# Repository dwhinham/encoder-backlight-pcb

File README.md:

# Rotary encoder backlight board

This simple board allows you to neatly and painlessly install LEDs on top of a rotary encoder for use with transparent/translucent knobs.

I designed this board when building a [MIDIbox SID synthesizer based on the MB6582 design][midibox-sid]. The idea was inspired by [Hawkeye's control surface build tutorial for the MB6582][knob-backlight-tutorial], but I didn't think I'd personally be able to do a very neat job with enamel wire, and so I decided to design a simple PCB to make it easier to achieve this kind of lighting.

The PCB has been verified to fit perfectly over [Alpha Taiwan RE160F-40E3-20A-24P-003][alpha-encoder] and [Bourns PEC16-4220F-N0024][bourns-encoder].

## Where can I get them?

- I have several spare sets available to anyone who wants them - [contact me on Twitter][twitter] if you'd like to buy some!
- I've also added the PCB to [OSH Park][osh-park] as a shared project if you'd like to order from there.
- Alternatively, you can download this repository and place your own order with a PCB fab service.

## Installation

The PCB has space for three surface-mount LEDs and one resistor. The size of all parts is **0603 imperial (1608 metric)**.

There are multiple **+ (positive)** terminals that you can use to daisy-chain multiple PCBs together if you need to.

### Choosing the resistor value

The three LEDs are wired in series, and share a common resistor (`R1`). The proper value for `R1` will vary depending on the specifications of your LED and the voltage of your power source.

If your LEDs have a low enough voltage drop, you may be able to just bridge `R1` (or use a 0 ohm resistor) and use a 5V power source. The [amber LEDs I used][amber-leds] did not light up at all this way however, and so I chose to use a 9V source instead.

You can use a [simple LED calculator][led-wizard] to help choose the right value for `R1`. In my case, using the datasheet for [my amber LEDs][amber-leds] I entered the following information into the calculator:

- Source voltage: **9V**
- Diode forward voltage: **2V**
- Diode forward current (mA): **20mA**
- Number of LEDs in your array: **3**

The result was **150 ohms**, and so that's the value I used for `R1`.

### Attaching the board to the encoder

1. Solder a wire to one or more of the **+ (positive)** terminal of the PCB. If space is limited above the encoder, it's recommended to solder the wire from the **back** of the board.
2. Take a small piece of rigid wire (the excess leads cut off from through-hole resistors or LEDs are ideal for this), and solder it to the ground terminal of your rotary encoder.
3. Bend a small "knee" in the wire so that it is fairly close to the "tongue" sticking out of the encoder, but not touching (see photo).
4. Place two small strips of adhesive foam on the front and back of the encoder (see photo). I recommend **3M PE foam tape** for this - it's very strong and thick enough to prevent shorts.
5. Place the PCB down over the encoder, ensuring the wire you soldered goes through the **- (negative)** hole.
6. Push down on the PCB to ensure it sticks nicely and then solder the negative wire.
7. Cut off the excess wire with a pair of wire cutters.
8. Make sure there are no shorts between the metal chassis of your encoders and any of the wires you have attached.
9. Repeat as necessary, daisy chaining the PCBs together via the **+ (positive)** terminals. The result should look like the photos below.

> **Note:** In the last photo above, the wires are shown above the PCBs. This was a mistake, as when test-fitting the metal front panel, there wasn't quite enough clearance, and so I moved them below the PCBs instead. I recommend you do the same.

[alpha-encoder]: https://www.mouser.co.uk/ProductDetail/318-ENC160F-24P
[amber-leds]: https://www.mouser.co.uk/ProductDetail/604-APT1608SYCK
[bourns-encoder]: https://www.mouser.co.uk/ProductDetail/652-PEC16-4220FN0024
[knob-backlight-tutorial]: http://midibox.org/forums/topic/14564-building-the-mb-6582-control-surface-photo-tutorial/?page=2#comment-139172
[led-wizard]: http://led.linear1.org/led.wiz
[midibox-sid]: http://www.midibox.org/dokuwiki/wilba_mb_6582
[osh-park]: https://oshpark.com/shared_projects/tsxIlm5c
[twitter]: https://twitter.com/_d0pefish_

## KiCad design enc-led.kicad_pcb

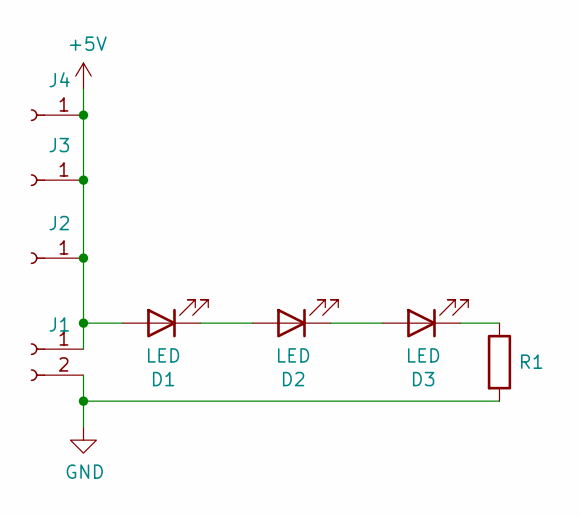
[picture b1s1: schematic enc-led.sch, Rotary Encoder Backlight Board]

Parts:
D1, D2, D3: LED; LED_0603_1608Metric
J1: Conn_01x02_Female; PinHeader_1x02_P2.54mm_Vertical
J2, J3, J4: Conn_01x01_Female; PinHeader_1x01_P2.54mm_Vertical
R1: R; R_0603_1608Metric

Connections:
+5V: D1.2 (A), J1.1, J2.1, J3.1, J4.1
GND: J1.2, R1.2
unnamed: D1.1 (K), D2.2 (A)
unnamed: D2.1 (K), D3.2 (A)
unnamed: D3.1 (K), R1.1

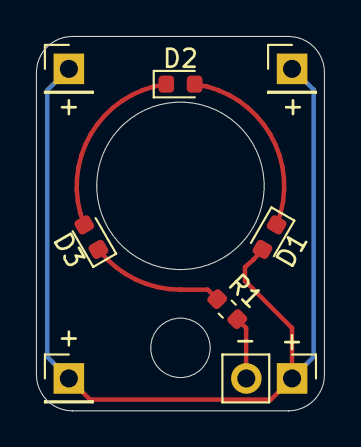
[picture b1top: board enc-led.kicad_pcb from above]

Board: 2 copper layers, 16.0 x 20.8 mm, 8 parts (0 on the bottom side), 5 nets.

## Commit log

2020-08-17 Fix typo in README.md

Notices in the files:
enc-led.kicad_pcb:
rev. 1 © 2020 dale w
